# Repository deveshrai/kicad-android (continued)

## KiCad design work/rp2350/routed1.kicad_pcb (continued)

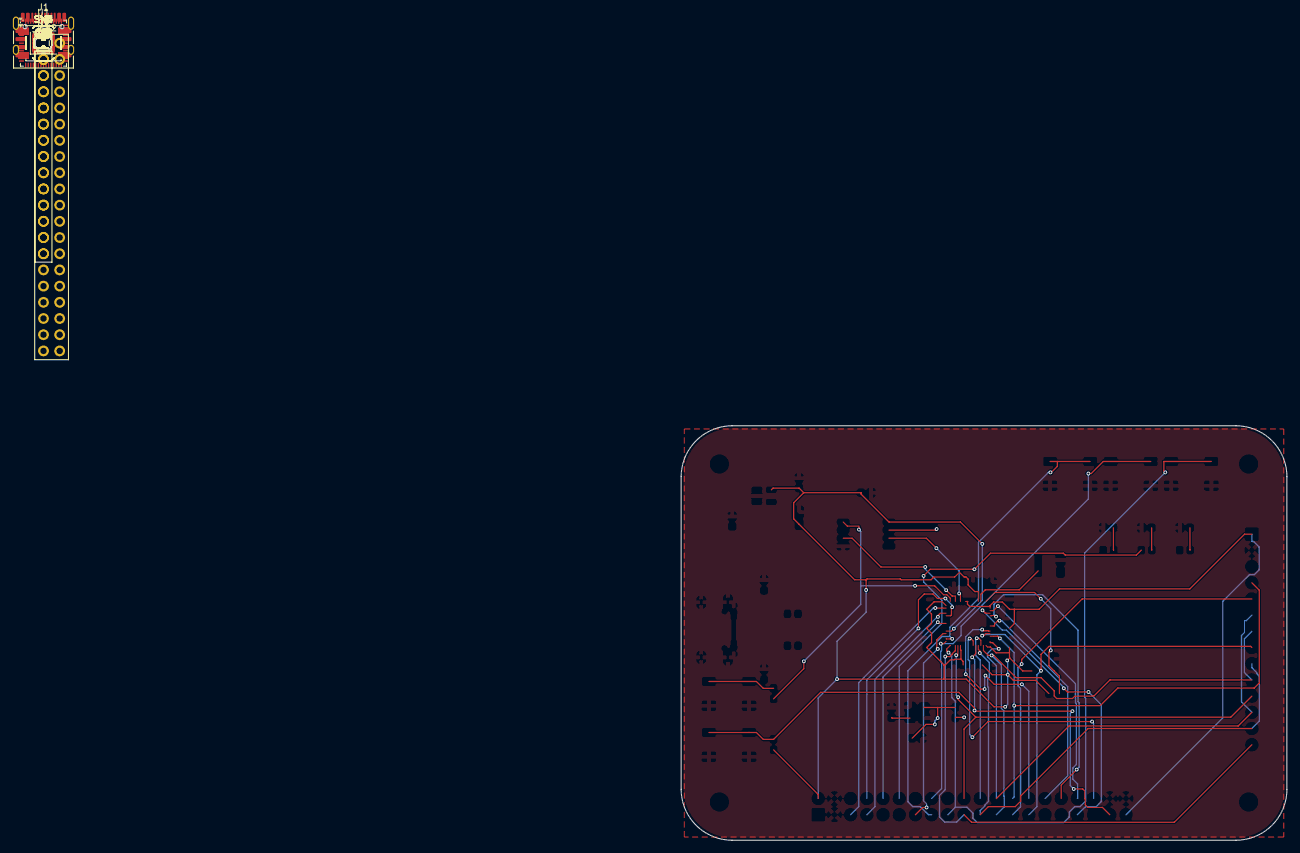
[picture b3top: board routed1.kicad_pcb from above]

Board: 2 copper layers, 95.0 x 65.0 mm, 52 parts (0 on the bottom side), 58 nets.

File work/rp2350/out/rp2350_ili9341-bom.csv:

"Item","Qty","References","Value","Footprint","Manufacturer","MPN","Description"
"1","2","C1,C2","1u","Capacitor_SMD:C_0603_1608Metric","Samsung","CL10A105KB8NNNC","Capacitor 1uF 50V X5R 10% 0603"
"2","1","C3","10u","Capacitor_SMD:C_0805_2012Metric","Samsung","CL21A106KAYNNNE","Capacitor 10uF 25V X5R 10% 0805"
"3","13","C4,C5,C6,C7,C8,C9,C10,C11,C12,C16,C17,C18,C19","100n","Capacitor_SMD:C_0603_1608Metric","Samsung","CL10B104KB8NNNC","Capacitor 100nF 50V X7R 10% 0603"
"4","3","C13,C14,C15","4.7u","Capacitor_SMD:C_0805_2012Metric","Samsung","CL21A475KAQNNNE","Capacitor 4.7uF 25V X5R 10% 0805"
"5","2","C20,C21","15p","Capacitor_SMD:C_0603_1608Metric","Samsung","CL10C150JB8NNNC","Capacitor 15pF 50V C0G 5% 0603"
"6","1","D1","Red","LED_SMD:LED_0603_1608Metric","Kingbright","APT1608EC","LED red 0603"
"7","1","D2","Green","LED_SMD:LED_0603_1608Metric","Kingbright","APT1608SGC","LED green 0603"
"8","1","D3","Blue","LED_SMD:LED_0603_1608Metric","Kingbright","APT1608QBC/D","LED blue 0603"
"9","1","J1","USB_C","Connector_USB:USB_C_Receptacle_HRO_TYPE-C-31-M-12","HRO","TYPE-C-31-M-12","USB-C receptacle USB 2.0 16-pin SMD"
"10","1","J2","IO","Connector_PinHeader_2.54mm:PinHeader_2x20_P2.54mm_Vertical","Sullins","PRPC020DAAN-RC","Male header 2x20 2.54mm vertical"
"11","1","J3","ILI9341_SPI","Connector_PinSocket_2.54mm:PinSocket_1x14_P2.54mm_Vertical","Sullins","PPTC141LFBN-RC","Female header 1x14 2.54mm vertical (ILI9341 2.8in module)"
"12","1","L1","3.3u","Inductor_SMD:L_Abracon_AOTA-B201610S","Abracon","AOTA-B201610S3R3-101-T","Power inductor 3.3uH 2016 (RP2350 core regulator)"
"13","2","R1,R2","5.1k","Resistor_SMD:R_0603_1608Metric","Yageo","RC0603FR-075K1L","Resistor 5.1k 1% 1/10W 0603"
"14","2","R3,R4","27","Resistor_SMD:R_0603_1608Metric","Yageo","RC0603FR-0727RL","Resistor 27R 1% 1/10W 0603"
"15","1","R5","33","Resistor_SMD:R_0603_1608Metric","Yageo","RC0603FR-0733RL","Resistor 33R 1% 1/10W 0603"
"16","2","R6,R7","1k","Resistor_SMD:R_0603_1608Metric","Yageo","RC0603FR-071KL","Resistor 1k 1% 1/10W 0603"
"17","1","R8","10k","Resistor_SMD:R_0603_1608Metric","Yageo","RC0603FR-0710KL","Resistor 10k 1% 1/10W 0603"
"18","3","R9,R10,R11","330","Resistor_SMD:R_0603_1608Metric","Yageo","RC0603FR-07330RL","Resistor 330R 1% 1/10W 0603"
"19","5","SW1,SW2,SW3,SW4,SW5","BOOTSEL,BTN1,BTN2,BTN3,RESET","Button_Switch_SMD:SW_SPST_TL3342","E-Switch","TL3342F160QG","Tactile switch SPST 4.2x3.2mm SMD 160gf"
"20","1","U1","RP2350A","Package_DFN_QFN:QFN-60-1EP_7x7mm_P0.4mm_EP3.4x3.4mm","Raspberry Pi","RP2350A","MCU RP2350A dual Cortex-M33/Hazard3 150MHz 520KB SRAM QFN-60 7x7"
"21","1","U2","AP2112K-3.3","Package_TO_SOT_SMD:SOT-23-5","Diodes Inc","AP2112K-3.3TRG1","LDO regulator 3.3V 600mA SOT-23-5"
"22","1","U3","W25Q128JVS","Package_SO:SOIC-8_5.3x5.3mm_P1.27mm","Winbond","W25Q128JVSIQ","QSPI NOR flash 128Mbit (16MB) SOIC-8 208mil"
"23","1","Y1","12MHz","Crystal:Crystal_SMD_3225-4Pin_3.2x2.5mm","Abracon","ABM8-272-T3","Crystal 12MHz 10pF 3225 4-pad"

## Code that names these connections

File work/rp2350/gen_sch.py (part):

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
# RP2350A
u1 = place('MCU_RaspberryPi:RP2350A', 'U1', 'RP2350A', 203.2, 152.4)
top_pins = {'1': '+3V3', '54': '+3V3', '53': '+3V3', '44': '+3V3', '49': '+3V3', '46': 'VREG_AVDD',
            '48': 'VREG_LX', '50': '+1V1', '6': '+1V1'}
for i, (num, net) in enumerate(top_pins.items()):
    connect(u1, num, net, stub=2.54 if i % 2 == 0 else 7.62)
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C('C13', '4.7u', x, 45.72, '+3V3', 'GND', C_FP_BULK); x += 7.62   # VREG_VIN
R('R5', '33', x, 45.72, '+3V3', 'VREG_AVDD'); x += 7.62
C('C14', '4.7u', x, 45.72, 'VREG_AVDD', 'GND', C_FP_BULK); x += 7.62
two_pin('Device:L_Small', 'L1', '3.3u', x, 45.72, 'VREG_LX', '+1V1',
        'Inductor_SMD:L_Abracon_AOTA-B201610S'); x += 7.62
C('C15', '4.7u', x, 45.72, '+1V1', 'GND', C_FP_BULK); x += 7.62
for i in range(3):
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# ILI9341 2.8" SPI module (14-pin header: VCC GND CS RESET DC SDI SCK LED SDO T_CLK T_CS T_DIN T_DO T_IRQ)
j3 = place('Connector_Generic:Conn_01x14', 'J3', 'ILI9341_SPI', 363.22, 76.2,
           'Connector_PinSocket_2.54mm:PinSocket_1x14_P2.54mm_Vertical')
for num, net in enumerate(['+3V3', 'GND', 'GPIO17', 'GPIO21', 'GPIO20', 'GPIO19', 'GPIO18',
                           'GPIO22', 'GPIO16', 'GPIO18', 'GPIO15', 'GPIO19', 'GPIO16', 'GPIO14'], 1):
    connect(j3, str(num), net)

# 2x20 IO header
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
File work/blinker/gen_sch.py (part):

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
# The timer
u = place('Timer:ICM7555xP', 'U1', 'ICM7555', 116.84, 76.2, 'Package_DIP:DIP-8_W7.62mm')
for pin, net in (('1', 'GND'), ('2', 'THR'), ('3', 'OUT'), ('4', 'VCC'), ('5', 'CV'),
                 ('6', 'THR'), ('7', 'DIS'), ('8', 'VCC')):
    connect(u, pin, net)

# Timing network
two_pin('Device:R', 'R1', '1k', 154.94, 55.88, 'VCC', 'DIS', R_THT)
two_pin('Device:R', 'R2', '47k', 154.94, 76.2, 'DIS', 'THR', R_THT)
two_pin('Device:C_Polarized', 'C1', '10u', 154.94, 99.06, 'THR', 'GND', 'Capacitor_THT:CP_Radial_D5.0mm_P2.00mm')
two_pin('Device:C', 'C2', '10n', 91.44, 104.14, 'CV', 'GND', C_DISC)
two_pin('Device:C', 'C3', '100n', 76.2, 50.8, 'VCC', 'GND', C_DISC)

# LED and its resistor (5 mm red LED, about 5 mA from 3 V)
# BLINKER_DEMO=1 leaves this stage out, so the README recording can draw it in the app
if not os.environ.get('BLINKER_DEMO'):
    two_pin('Device:R', 'R3', '220', 185.42, 66.04, 'OUT', 'LED_A', R_THT)
    two_pin('Device:LED', 'D1', 'Red 5mm', 185.42, 88.9, 'GND', 'LED_A', 'LED_THT:LED_D5.0mm')

# Power flag: GND comes from the cell, which has no power output pin
for i, (net, xx) in enumerate((('GND', 30.48),)):
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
